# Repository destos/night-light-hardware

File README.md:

# night-light-hardware

Eagle files for a night light projects that wraps around an Apple iPhone power brick.

[Arduino Code](https://github.com/destos/night-light-arduino)

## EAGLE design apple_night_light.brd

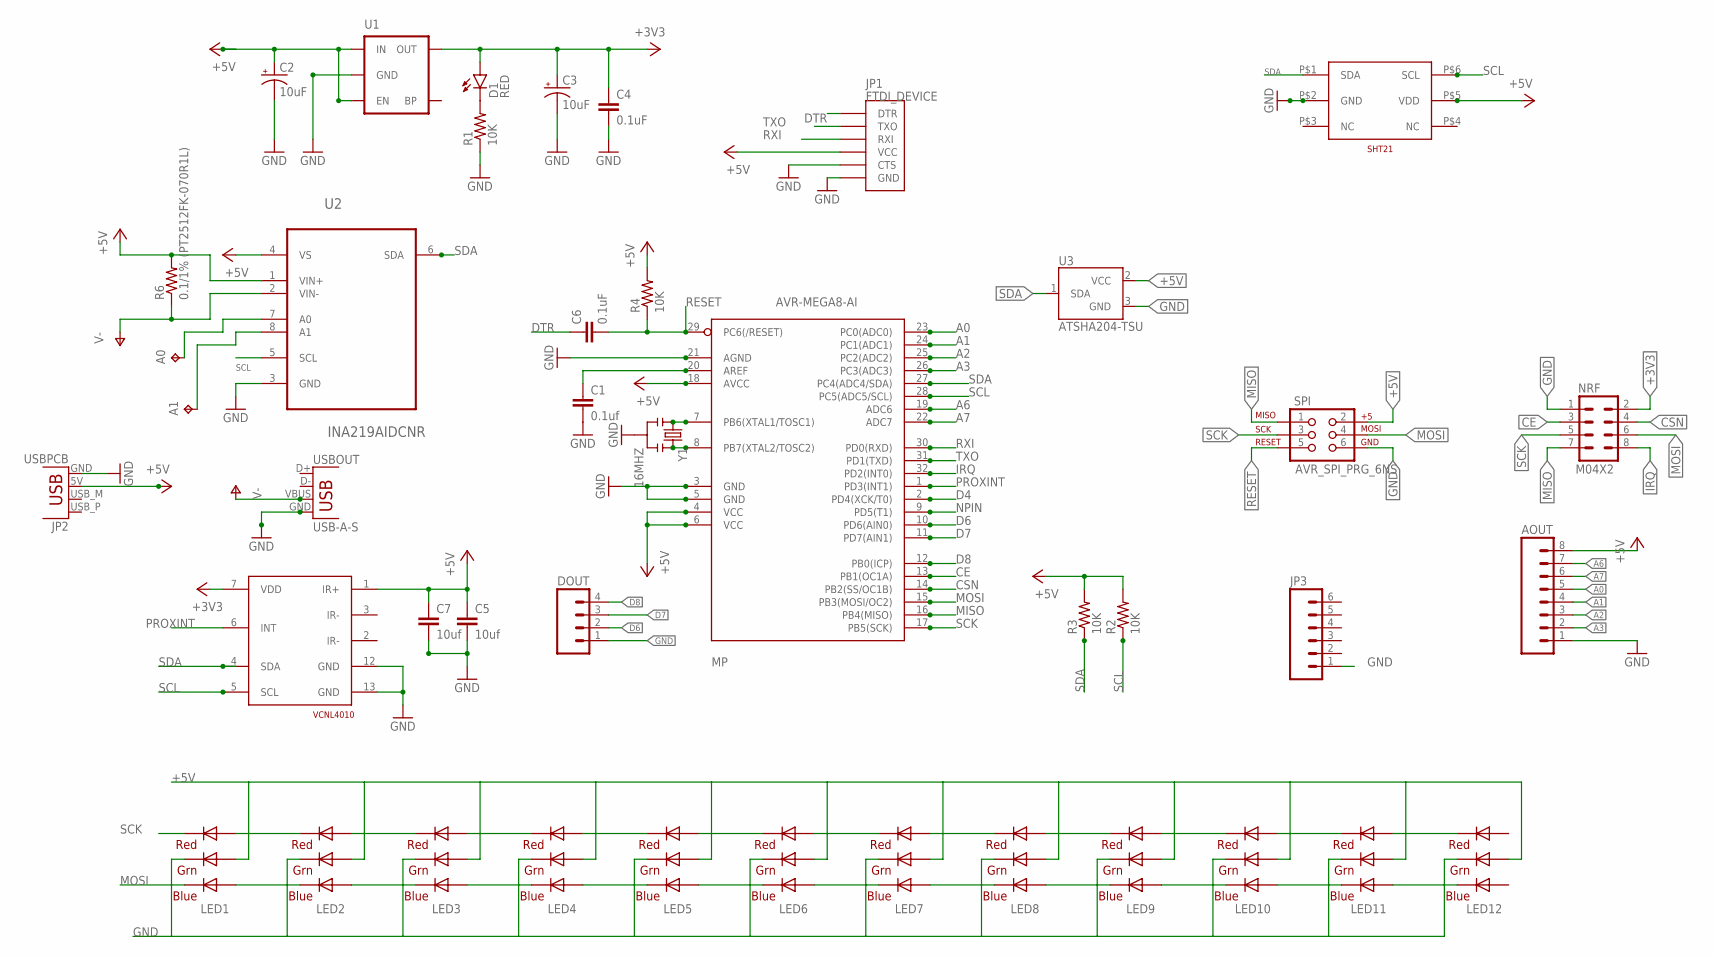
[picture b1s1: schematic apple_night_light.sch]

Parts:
A0, A1: TPB1,27; B1,27
AOUT: M08LOCK; 1X08_LOCK
C1: 0.1uf; 0805
C2, C3: 10uF; EIA3216
C4, C6: 0.1uF; 0603-CAP
C5, C7: 10uf; 0805
D1: RED; LED-0603
DOUT: M04LOCK; 1X04_LOCK
JP1: FTDI_DEVICE; FTDI_DEVICE_SIDE
JP2: USBPCB; USB-A-PCB
JP3: M06NO_SILK_FEMALE_PTH; 1X06_NO_SILK
LED1, LED2, LED3, LED4, LED5, LED6, LED7, LED8, LED9, LED10, LED11, LED12: RGBLED5050
MP: AVR-MEGA8-AI; TQFP32-08
NRF: M04X2; 2X4
R1, R2, R3, R4: 10K; 0603-RES
R6: 0.1/1% (PT2512FK-070R1L); R2512
SPI: AVR_SPI_PRG_6NS; 2X3-NS
U1: MIC52053.3V; SOT23-5
U2: INA219AIDCNR; SOT65P280X145-8N
U3: ATSHA204-TSU; SOT23-3
U$1: SHT21; DFN6
U$3: VCNL4010
USBOUT: USB-A-S
Y1: 16MHZ; RESONATOR-SMD

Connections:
+3V3: C3.A (+), C4.1, D1.A, NRF.2, U1.5 (OUT), U$3.7 (VDD)
+5V: AOUT.8, C2.A (+), C5.1, C7.1, JP1.P$4 (VCC), JP2.5V (VBUS), LED1.1 (GREEN_A), LED2.1 (GREEN_A), LED3.1 (GREEN_A), LED4.1 (GREEN_A), LED5.1 (GREEN_A), LED6.1 (GREEN_A), LED7.1 (GREEN_A), LED8.1 (GREEN_A), LED9.1 (GREEN_A), LED10.1 (GREEN_A), LED11.1 (GREEN_A), LED12.1 (GREEN_A), MP.4 (VCC), MP.6 (VCC), MP.18 (AVCC), R2.2, R3.2, R4.2, R6.2, SPI.2, U1.1 (IN), U1.3 (EN), U2.1 (VIN+), U2.4 (VS), U3.2 (VCC), U$1.P$5 (VDD), U$3.1 (IR+)
A0: AOUT.5, MP.23 (PC0(ADC0))
A1: AOUT.4, MP.24 (PC1(ADC1))
A2: AOUT.3, MP.25 (PC2(ADC2))
A3: AOUT.2, MP.26 (PC3(ADC3))
A6: AOUT.7, MP.19 (ADC6)
A7: AOUT.6, MP.22 (ADC7)
APACI1: LED3.2 (RED_A), LED4.5 (RED_C)
APACI2: LED6.2 (RED_A), LED7.5 (RED_C)
APACI3: LED9.2 (RED_A), LED10.5 (RED_C)
CE: MP.13 (PB1(OC1A)), NRF.3
CSN: MP.14 (PB2(SS/OC1B)), NRF.4
D4: MP.2 (PD4(XCK/T0))
D6: DOUT.2, MP.10 (PD6(AIN0))
D7: DOUT.3, MP.11 (PD7(AIN1))
D8: DOUT.4, MP.12 (PB0(ICP))
DTR: C6.1, JP1.P$1 (DTR)
GND: AOUT.1, C1.2, C2.C (-), C3.C (-), C4.2, C5.2, C7.2, DOUT.1, JP1.P$5 (CTS), JP1.P$6 (GND), JP2.GND, JP3.1, LED1.6 (GREEN_C), LED2.6 (GREEN_C), LED3.6 (GREEN_C), LED4.6 (GREEN_C), LED5.6 (GREEN_C), LED6.6 (GREEN_C), LED7.6 (GREEN_C), LED8.6 (GREEN_C), LED9.6 (GREEN_C), LED10.6 (GREEN_C), LED11.6 (GREEN_C), LED12.6 (GREEN_C), MP.3 (GND), MP.5 (GND), MP.21 (AGND), NRF.1, R1.1, SPI.6, U1.2 (GND), U2.3 (GND), U3.3 (GND), U$1.P$2 (GND), U$3.12 (GND), U$3.13 (GND), USBOUT.GND, Y1.2
IR-: U$3.2 (IR-), U$3.3 (IR-)
IRQ: MP.32 (PD2(INT0)), NRF.8
MISO: MP.16 (PB4(MISO)), NRF.7, SPI.1
MOSI: LED1.4 (BLUE_C), MP.15 (PB3(MOSI/OC2)), NRF.6, SPI.4
unnamed: LED1.2 (RED_A), LED2.5 (RED_C)
unnamed: LED2.2 (RED_A), LED3.5 (RED_C)
unnamed: LED1.3 (BLUE_A), LED2.4 (BLUE_C)
unnamed: LED2.3 (BLUE_A), LED3.4 (BLUE_C)
unnamed: LED3.3 (BLUE_A), LED4.4 (BLUE_C)
unnamed: C1.1, MP.20 (AREF)
unnamed: LED6.3 (BLUE_A), LED7.4 (BLUE_C)
unnamed: MP.8 (PB7(XTAL2/TOSC2)), Y1.3
unnamed: MP.7 (PB6(XTAL1/TOSC1)), Y1.1
unnamed: LED9.3 (BLUE_A), LED10.4 (BLUE_C)
unnamed: LED4.2 (RED_A), LED5.5 (RED_C)
unnamed: LED5.2 (RED_A), LED6.5 (RED_C)
unnamed: LED4.3 (BLUE_A), LED5.4 (BLUE_C)
unnamed: LED5.3 (BLUE_A), LED6.4 (BLUE_C)
unnamed: LED7.2 (RED_A), LED8.5 (RED_C)
unnamed: LED8.2 (RED_A), LED9.5 (RED_C)
unnamed: LED7.3 (BLUE_A), LED8.4 (BLUE_C)
unnamed: LED8.3 (BLUE_A), LED9.4 (BLUE_C)
unnamed: D1.C, R1.2
unnamed: LED10.2 (RED_A), LED11.5 (RED_C)
unnamed: LED11.2 (RED_A), LED12.5 (RED_C)
unnamed: LED10.3 (BLUE_A), LED11.4 (BLUE_C)
unnamed: LED11.3 (BLUE_A), LED12.4 (BLUE_C)
unnamed: A0.TP, U2.7 (A0)
unnamed: A1.TP, U2.8 (A1)
NPIN: MP.9 (PD5(T1))
PROXINT: MP.1 (PD3(INT1)), U$3.6 (INT)
RESET: C6.2, MP.29 (PC6(/RESET)), R4.1, SPI.5
RXI: JP1.P$3 (RXI), MP.30 (PD0(RXD))
SCK: LED1.5 (RED_C), MP.17 (PB5(SCK)), NRF.5, SPI.3
SCL: MP.28 (PC5(ADC5/SCL)), R2.1, U2.5 (SCL), U$1.P$6 (SCL), U$3.5 (SCL)
SDA: MP.27 (PC4(ADC4/SDA)), R3.1, U2.6 (SDA), U3.1 (SDA), U$1.P$1 (SDA), U$3.4 (SDA)
TXO: JP1.P$2 (TXO), MP.31 (PD1(TXD))
V-: R6.1, U2.2 (VIN-), USBOUT.VBUS

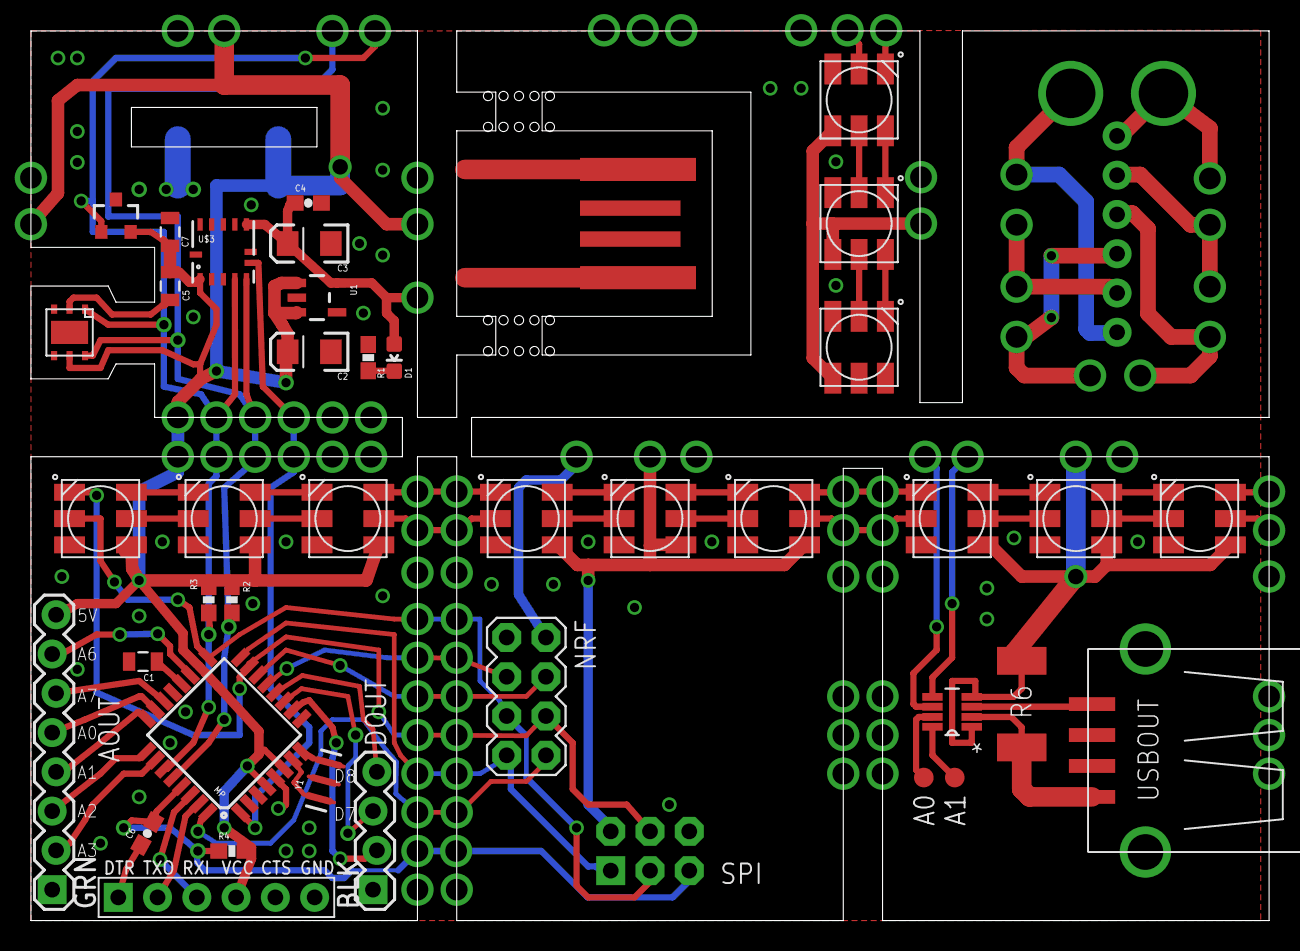
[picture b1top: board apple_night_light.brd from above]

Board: 2 copper layers, 80.1 x 57.5 mm, 42 parts (0 on the bottom side), 55 nets.

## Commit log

2015-01-02 first board commit, some work done on schematics and layout
2015-01-03 some routing, adding current sensor, ground pours
2015-01-03 usb passthrough placed, better routing on neopixel power
2015-01-07 moved and corrected currentsensor, trying to fix clearances, adding temp/humidity sensor
2015-01-13 adding board snapshot
2015-02-18 before removing the nrf chip for breakout board
2015-03-03 more stuff, adding crypto board
2015-03-04 layout power, move usb connector to save money, trying to finalize
2015-03-04 adding oshpark preview before dotstar conversion
2015-03-04 converting to dotstar LEDs, still some hookup work needed
2015-03-04 more work on dotstar routing
2015-03-21 re-laying out the board and separating panels to an extent
2015-03-27 adding balance board for space usage, tightening things up
2015-03-28 final changes before order, reversing tx/rx for ftdi, reset pin on SPI
2015-03-28 adding updated images
2015-04-18 fixing issue with grounding VCNL IR emmiter, causes blow out of emmiter :x

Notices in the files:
parts and their libraries:
SparkFun-Capacitors: Licensing: Creative Commons ShareAlike 4.0 International - https://creativecommons.org/licenses/by-sa/4.0
